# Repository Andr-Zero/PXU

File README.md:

# PXU - Replacement Power Supply for the Orignial Xbox!

## 🛑 VERY IMPORTANT SAFETY DISCLAIMER 🛑
This project involves working with and replacing a power supply unit that was originally designed to handle mains voltage. The original OEM power supply can retain a lethal electrical charge long after it has been unplugged. Proceed with extreme caution.

 **HIGH VOLTAGE RISK**: You are solely responsible for your safety. Improper handling of electronics can lead to serious injury, death, or fire. If you are not experienced and confident in working with electronics, do not attempt to install this hardware.

**USE AT YOUR OWN RISK**: This is a hobbyist project provided "as is" without warranties of any kind. The author, Andr0, is not responsible for any damage to your console, other property, or any personal injury that may occur from the use or misuse of this hardware.
___
## Features
-   ✨Support 1.0 through 1.6 revisions consoles! ✨  
    *1.0/1.1 requires the proper 12-pin connector.  
    *Switching between 1.0-1.4 and 1.6s requires changing several zero ohm resistors, documented on bottom of the PCB.
-   Accepts any DC input from 16-20V, 100W+ (Including 100W USB-C PD chargers).
-   Features user-replaceable input modules.
-   Designed as a direct swap with the OEM power supply, using the same mounting points.

## Installation
**Warning:** The OEM power supply can be dangerous even after being unplugged for long periods. Proceed with caution!

1.  **Make sure the AC power cord is unplugged from the wall!** Then, press the Xbox's power button a few times to help discharge any residual power.
2.  Open the console and remove the hard drive tray.
3.  Unplug the cable connecting the OEM power supply to the mainboard.
4.  Remove the two screws holding the power supply down. Slide it toward the front of the console just enough to disengage it from the shell's retaining clips.
5.  The power supply should now lift out. You may need to angle it to get it out of the shell.
6.  Installation is the reverse of this process.

## FAQ
**Will my "******"  work as a power source?** I cannot test every power source available. I have personally tested an MSI laptop charger (180W) and an Anker 100W USB-C charger. Similar adapters that meet the specification of 16-20V and can deliver 100W or more should work.

**Can you add feature "X"?** The goal of the main PXU board is to be a drop-in replacement that powers the console just like the OEM supply. Additional features can and should be added as daughterboards using the provided mount points.

**I dont see the USB-C Board Here.** That's in another repo: https://github.com/Andr-Zero/PXU-C-PIM

## License

This project is open-source hardware, licensed under the **CERN-OHL-S v2** (CERN Open Hardware Licence - Strongly Reciprocal).

**Copyright © 2025 Andr0**

You are free to:

-   **Use and reproduce** this design for any purpose.
-   **Modify** the design to fit your needs.  
-   **Distribute** the original design or your modifications.

In return, you must:

-   **Give credit**
-   **Share your changes** under the same CERN-OHL-S v2 license.
-  **Keep all copyright and license notices intact.** As a condition of the license's attribution requirement, all original markings on the PCB silkscreen must be retained. This includes the copyright notice, the PXU and Team Resurgent logos, and any project URLs present in the original design files. These should not be removed or altered.

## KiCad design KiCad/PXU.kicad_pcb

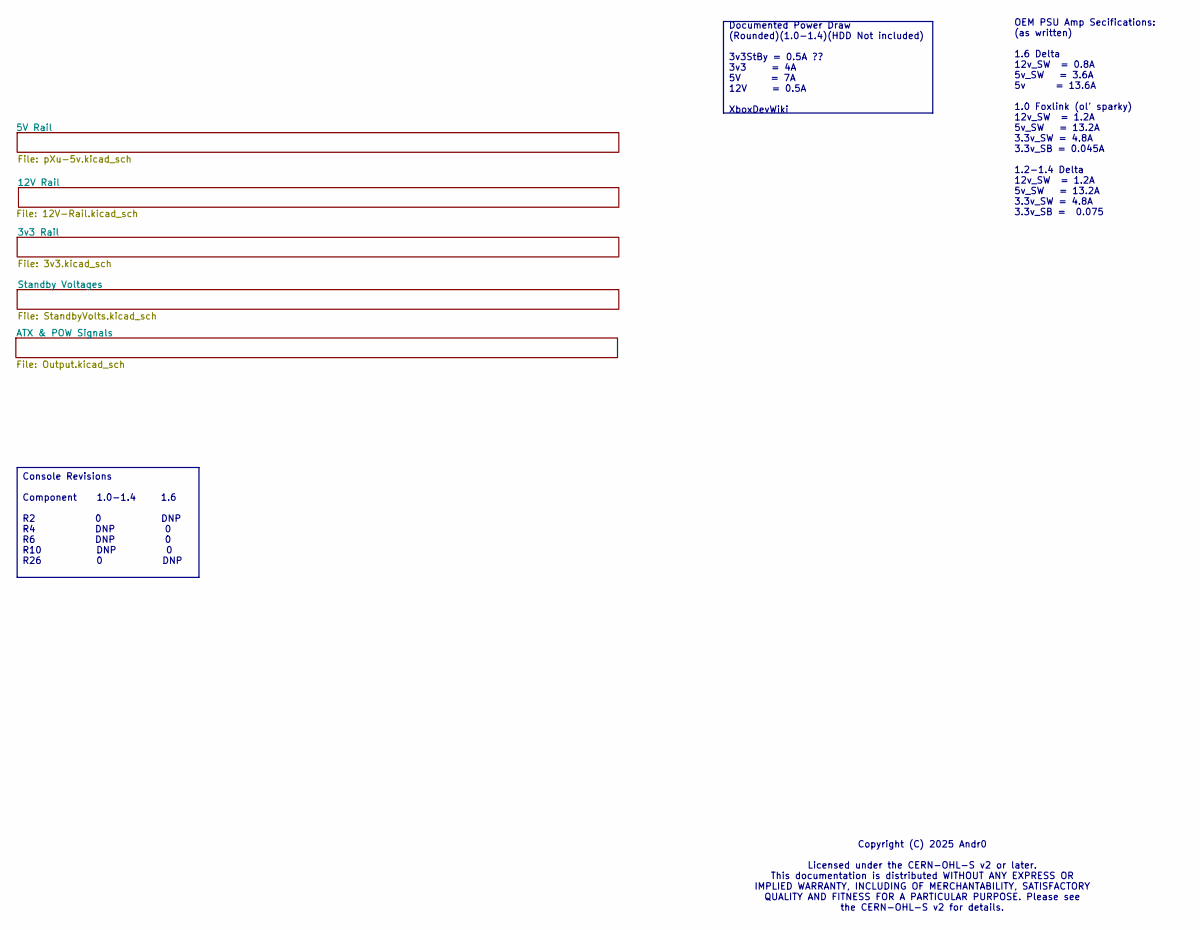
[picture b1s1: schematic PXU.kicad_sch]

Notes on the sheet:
OEM PSU Amp Secifications: (as written) 1.6 Delta 12v_SW = 0.8A 5v_SW = 3.6A 5v = 13.6A 1.0 Foxlink (ol' sparky) 12v_SW = 1.2A 5v_SW = 13.2A 3.3v_SW = 4.8A 3.3v_SB = 0.045A 1.2-1.4 Delta 12v_SW = 1.2A 5v_SW = 13.2A 3.3v_SW = 4.8A 3.3v_SB = 0.075
Copyright (C) 2025 Andr0 Licensed under the CERN-OHL-S v2 or later. This documentation is distributed WITHOUT ANY EXPRESS OR IMPLIED WARRANTY, INCLUDING OF MERCHANTABILITY, SATISFACTORY QUALITY AND FITNESS FOR A PARTICULAR PURPOSE. Please see the CERN-OHL-S v2 for details.
Console Revisions Component 1.0-1.4 1.6 R2 0 DNP R4 DNP 0 R6 DNP 0 R10 DNP 0 R26 0 DNP
Documented Power Draw (Rounded)(1.0-1.4)(HDD Not included) 3v3StBy = 0.5A ?? 3v3 = 4A 5V = 7A 12V = 0.5A XboxDevWiki

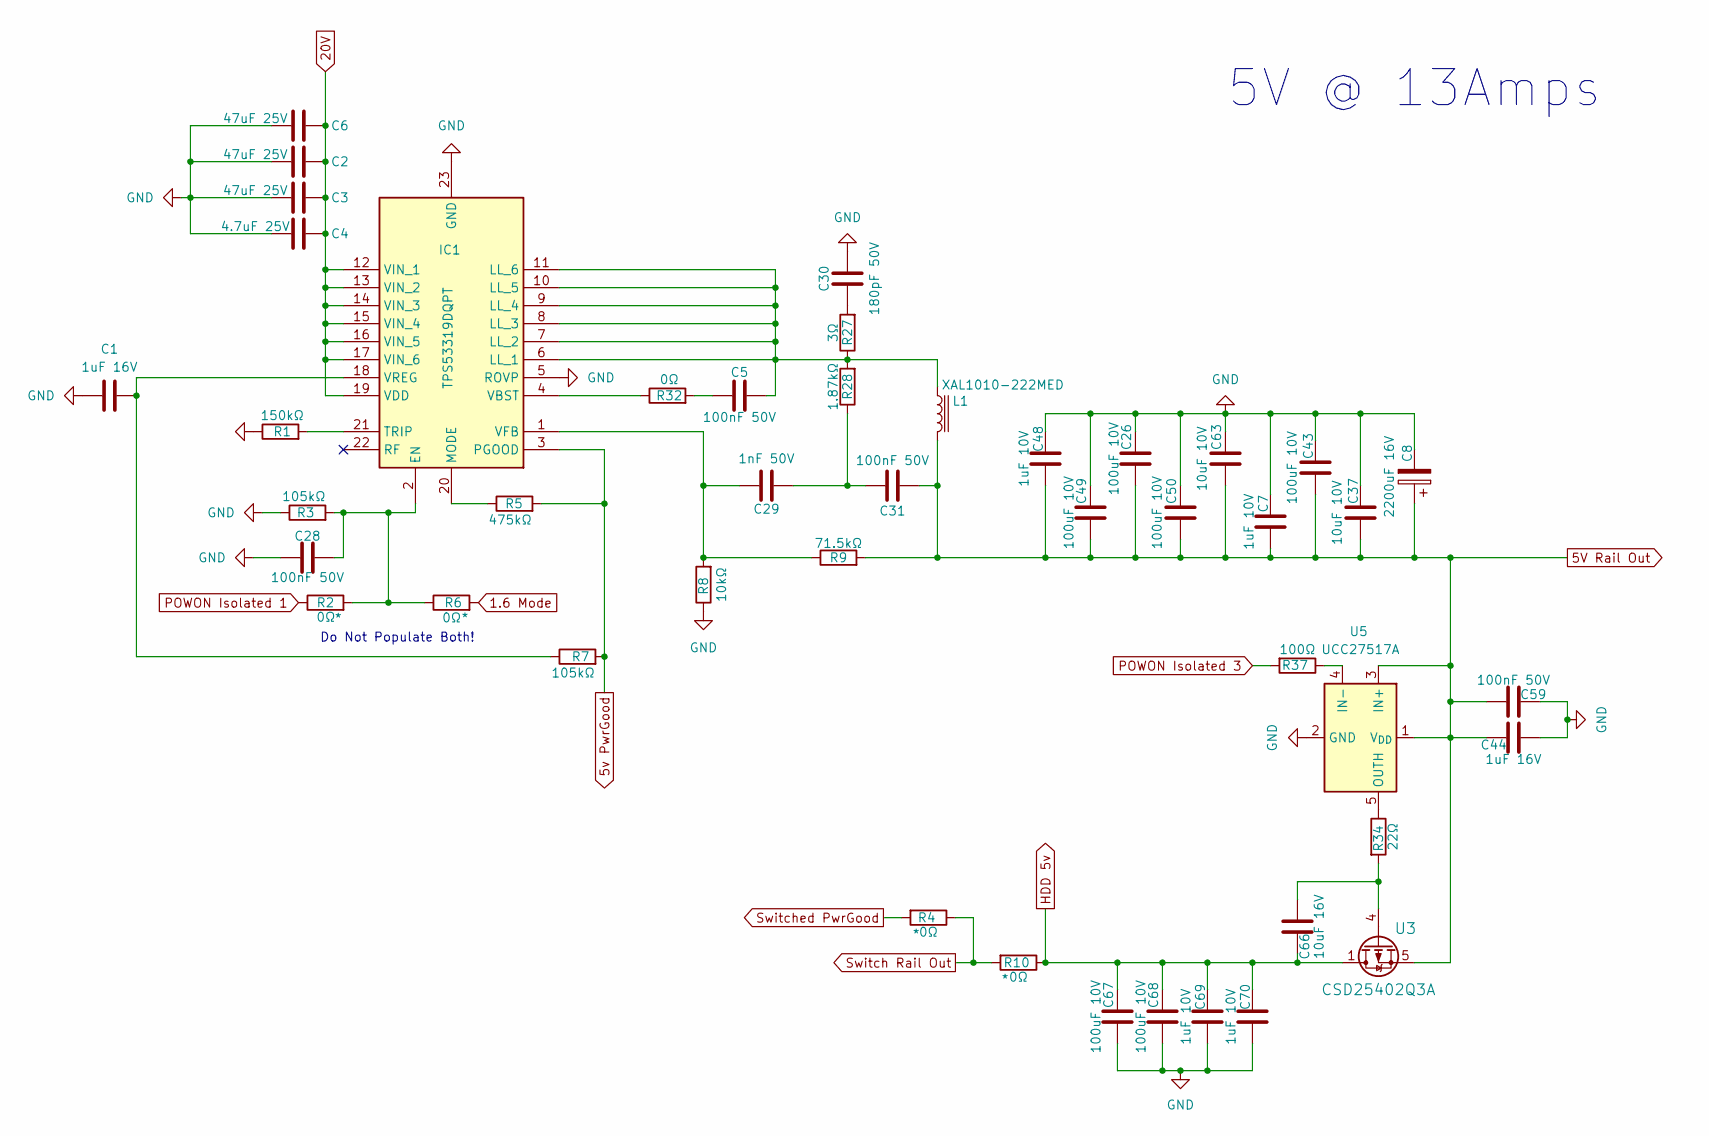
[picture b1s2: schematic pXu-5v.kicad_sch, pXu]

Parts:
C1, C44: 1uF 16V; C_0603_1608Metric_Pad1.08x0.95mm_HandSolder
C2, C3, C6: 47uF 25V; C_1210_3225Metric_Pad1.33x2.70mm_HandSolder
C4: 4.7uF 25V; C_0603_1608Metric_Pad1.08x0.95mm_HandSolder
C5, C28, C31, C59: 100nF 50V; C_0603_1608Metric_Pad1.08x0.95mm_HandSolder
C7, C48, C69, C70: 1uF 10V; C_0603_1608Metric_Pad1.08x0.95mm_HandSolder
C8: 2200uF 16V; CP_Radial_D10.0mm_P5.00mm
C26, C43, C49, C50, C67, C68: 100uF 10V; C_1206_3216Metric_Pad1.33x1.80mm_HandSolder
C29: 1nF 50V; C_0603_1608Metric_Pad1.08x0.95mm_HandSolder
C30: 180pF 50V; C_0603_1608Metric_Pad1.08x0.95mm_HandSolder
C37, C63: 10uF 10V; C_0805_2012Metric_Pad1.18x1.45mm_HandSolder
C66: 10uF 16V; C_0603_1608Metric_Pad1.08x0.95mm_HandSolder
IC1: TPS53319DQPT; SON50P500X600X150-23N-D; Mouser Part Number 595-TPS53319DQPT
L1: XAL1010-222MED; L_10.4x10.4_H4.8; Part# XAL1010-222MED
R1: 150kΩ; R_0603_1608Metric_Pad0.98x0.95mm_HandSolder
R2, R4, R6, R32: 0Ω; R_0603_1608Metric_Pad0.98x0.95mm_HandSolder
R3, R7: 105kΩ; R_0603_1608Metric_Pad0.98x0.95mm_HandSolder
R5: 475kΩ; R_0603_1608Metric_Pad0.98x0.95mm_HandSolder
R8: 10kΩ; R_0603_1608Metric_Pad0.98x0.95mm_HandSolder
R9: 71.5kΩ; R_0603_1608Metric_Pad0.98x0.95mm_HandSolder
R10: 0Ω; R_1206_3216Metric_Pad1.30x1.75mm_HandSolder
R27: 3Ω; R_1206_3216Metric_Pad1.30x1.75mm_HandSolder
R28: 1.87kΩ; R_0805_2012Metric_Pad1.20x1.40mm_HandSolder
R34: 22Ω; R_0603_1608Metric_Pad0.98x0.95mm_HandSolder
R37: 100Ω; R_0603_1608Metric_Pad0.98x0.95mm_HandSolder
U3: CSD25402Q3A; VSON-8_3.3x3.3mm_P0.65mm_NexFET
U5: UCC27517A; SOT-23-5

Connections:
1.6 Mode: R6.2; also elsewhere on the board
5V Rail Out: C7.2, C8.1, C26.2, C31.1, C37.2, C43.2, C44.1, C48.2, C49.2, C50.2, C59.2, C63.2, L1.2, R9.2, U3.5 (S), U5.1 (V_{DD}), U5.3 (IN+); also elsewhere on the board
5v PwrGood: IC1.3 (PGOOD), R5.2, R7.2; also elsewhere on the board
20V: C2.2, C3.2, C4.2, C6.2, IC1.12 (VIN_1), IC1.13 (VIN_2), IC1.14 (VIN_3), IC1.15 (VIN_4), IC1.16 (VIN_5), IC1.17 (VIN_6), IC1.19 (VDD); also elsewhere on the board
GND: C1.1, C2.1, C3.1, C4.1, C6.1, C7.1, C8.2, C26.1, C28.1, C30.2, C37.1, C43.1, C44.2, C48.1, C49.1, C50.1, C59.1, C63.1, C67.2, C68.2, C69.2, C70.2, IC1.5 (ROVP), IC1.23 (GND), R1.1, R3.1, R8.1, U5.2 (GND); also elsewhere on the board
HDD 5v: C66.1, C67.1, C68.1, C69.1, C70.1, R10.1, U3.1 (D), U3.2 (D), U3.3 (D); also elsewhere on the board
unnamed: C5.2, R32.2
unnamed: C29.1, C31.2, R28.1
unnamed: C30.1, R27.2
unnamed: C28.2, IC1.2 (EN), R2.2, R3.2, R6.1
unnamed: C5.1, IC1.6 (LL_1), IC1.7 (LL_2), IC1.8 (LL_3), IC1.9 (LL_4), IC1.10 (LL_5), IC1.11 (LL_6), L1.1, R27.1, R28.2
unnamed: IC1.20 (MODE), R5.1
unnamed: IC1.21 (TRIP), R1.2
unnamed: IC1.4 (VBST), R32.1
unnamed: C29.2, IC1.1 (VFB), R8.2, R9.1
unnamed: C1.2, IC1.18 (VREG), R7.1
unnamed: C66.2, R34.2, U3.4 (G)
unnamed: R37.1, U5.4 (IN-)
unnamed: R34.1, U5.5 (OUTH)
POWON Isolated 1: R2.1; also elsewhere on the board
POWON Isolated 3: R37.2; also elsewhere on the board
Switch Rail Out: R4.1, R10.2; also elsewhere on the board
Switched PwrGood: R4.2; also elsewhere on the board

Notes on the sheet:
Do Not Populate Both!
5V @ 13Amps

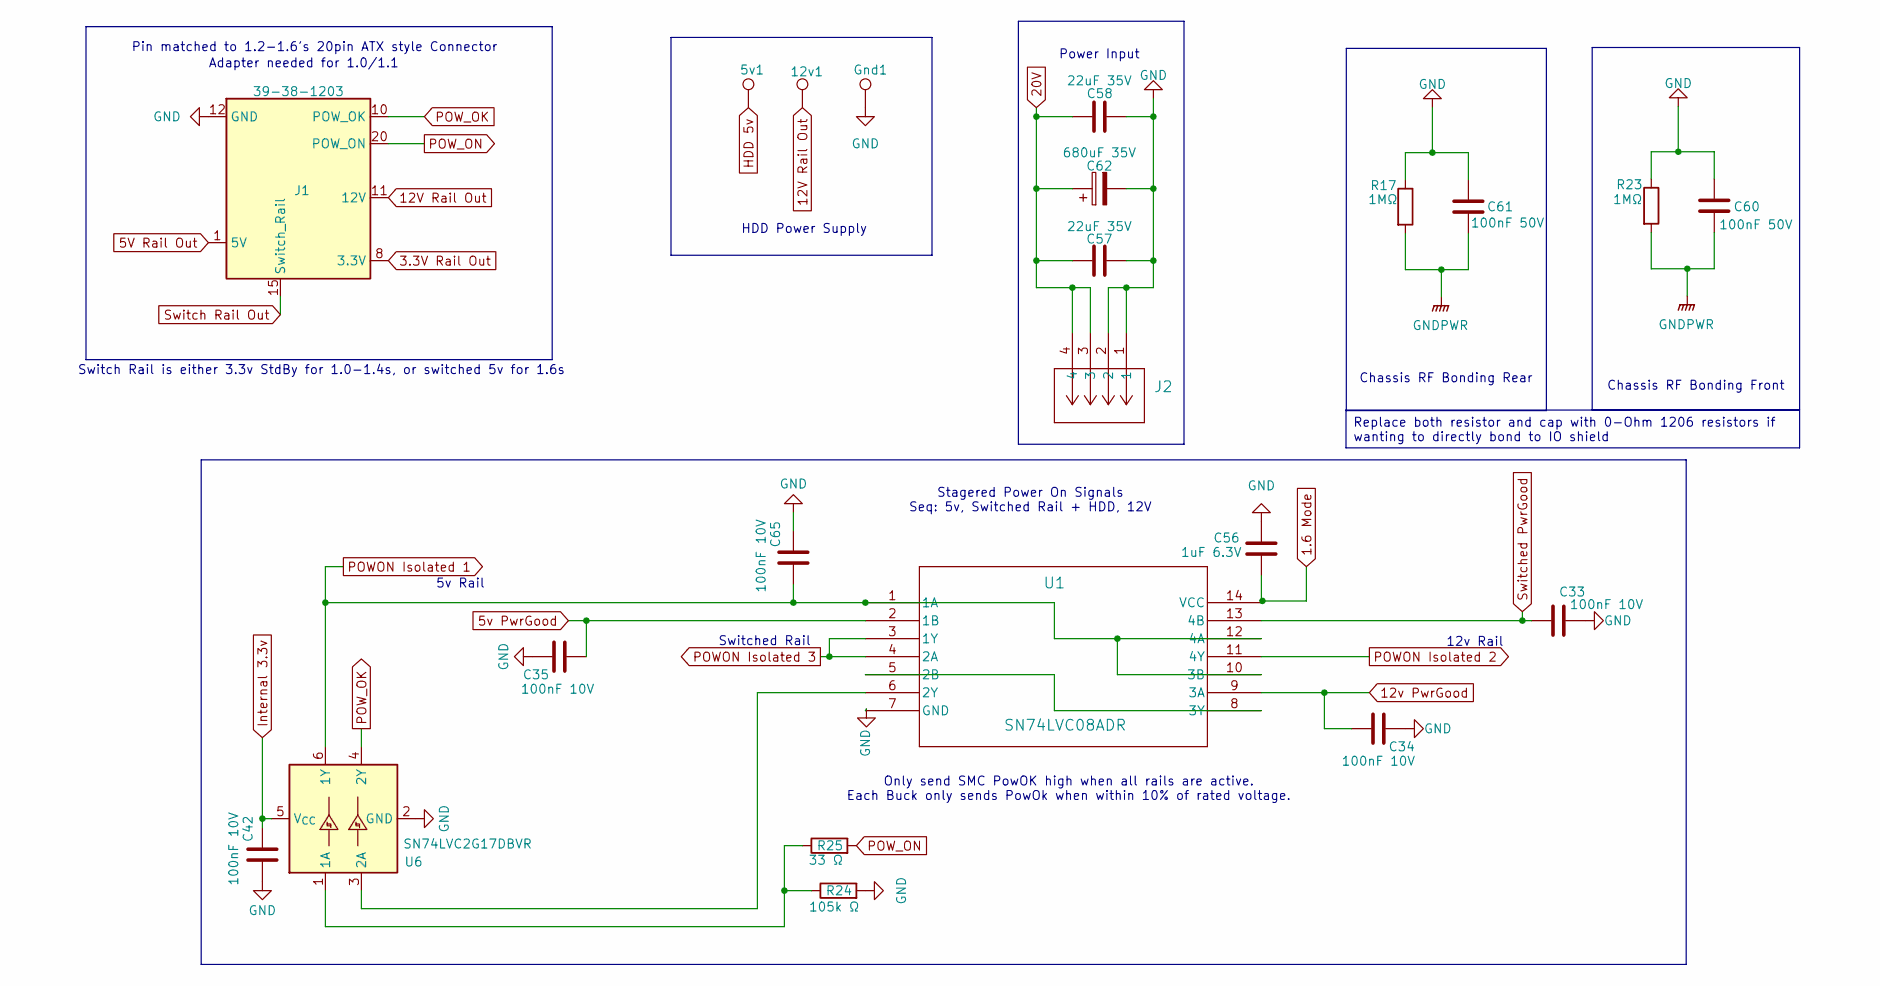
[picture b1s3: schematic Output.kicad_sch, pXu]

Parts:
5v1, 12v1: TestPoint; TestPoint_THTPad_D4.0mm_Drill2.0mm
C33, C34, C35, C42, C65: 100nF 10V; C_0603_1608Metric_Pad1.08x0.95mm_HandSolder
C56: 1uF 6.3V; C_0603_1608Metric_Pad1.08x0.95mm_HandSolder
C57, C58: 22uF 35V; C_1210_3225Metric_Pad1.33x2.70mm_HandSolder
C60, C61: 100nF 50V; C_1206_3216Metric_Pad1.33x1.80mm_HandSolder
C62: 680uF 35V; CP_Radial_D10.0mm_P5.00mm
Gnd1: TestPoint; TestPoint_THTPad_D4.0mm_Drill2.0mm
J1: 39-38-1203; Molex_Mini-Fit_Jr_5566-20A_2x10_P4.20mm_Vertical
J2: 171826-4; CONN_171826-4_TYCO_TYC
R17, R23: 1MΩ; R_1206_3216Metric_Pad1.30x1.75mm_HandSolder
R24: 105k Ω; R_0603_1608Metric_Pad0.98x0.95mm_HandSolder
R25: 33 Ω; R_0603_1608Metric_Pad0.98x0.95mm_HandSolder
U1: SN74LVC08ADR; D14
U6: SN74LVC2G17DBVR; SOT-23-6_Handsoldering

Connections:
1.6 Mode: C42.2, C56.2, U1.14 (VCC), U6.5 (V_{CC}); also elsewhere on the board
3.3V Rail Out: J1.7 (3.3V), J1.8 (3.3V), J1.17 (3.3V), J1.18 (3.3V); also elsewhere on the board
5V Rail Out: J1.1 (5V), J1.2 (5V), J1.3 (5V), J1.13 (5V); also elsewhere on the board
5v PwrGood: C35.2, U1.2 (1B); also elsewhere on the board
12V Rail Out: 12v1.1, J1.11 (12V); also elsewhere on the board
12v PwrGood: C34.1, U1.9 (3A); also elsewhere on the board
20V: C57.1, C58.1, C62.1, J2.3, J2.4; also elsewhere on the board
GND: C33.1, C34.2, C35.1, C42.1, C56.1, C57.2, C58.2, C60.1, C61.1, C62.2, C65.1, Gnd1.1, J1.4 (GND), J1.5 (GND), J1.6 (GND), J1.9 (GND), J1.12 (GND), J1.14 (GND), J1.16 (GND), J1.19 (GND), J2.1, J2.2, R17.1, R23.1, R24.2, U1.7 (GND), U6.2 (GND); also elsewhere on the board
GNDPWR: C60.2, C61.2, R17.2, R23.2
unnamed: U1.5 (2B), U1.8 (3Y)
unnamed: U1.6 (2Y), U6.3 (2A)
unnamed: R24.1, R25.1, U6.1 (1A)
POWON Isolated 1: C65.2, U1.1 (1A), U1.10 (3B), U1.12 (4A), U6.6 (1Y); also elsewhere on the board
POWON Isolated 2: U1.11 (4Y); also elsewhere on the board
POWON Isolated 3: U1.3 (1Y), U1.4 (2A); also elsewhere on the board
POW_OK: J1.10 (POW_OK), U6.4 (2Y)
POW_ON: J1.20 (POW_ON), R25.2
Switch Rail Out: J1.15 (Switch_Rail); also elsewhere on the board
Switched PwrGood: C33.2, U1.13 (4B); also elsewhere on the board

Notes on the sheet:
HDD Power Supply
Switched Rail
Chassis RF Bonding Rear
Adapter needed for 1.0/1.1
Pin matched to 1.2-1.6's 20pin ATX style Connector
Stagered Power On Signals Seq: 5v, Switched Rail + HDD, 12V
12v Rail
Only send SMC PowOK high when all rails are active. Each Buck only sends PowOk when within 10% of rated voltage.
Power Input
Chassis RF Bonding Front
5v Rail
Switch Rail is either 3.3v StdBy for 1.0-1.4s, or switched 5v for 1.6s
Replace both resistor and cap with 0-Ohm 1206 resistors if wanting to directly bond to IO shield

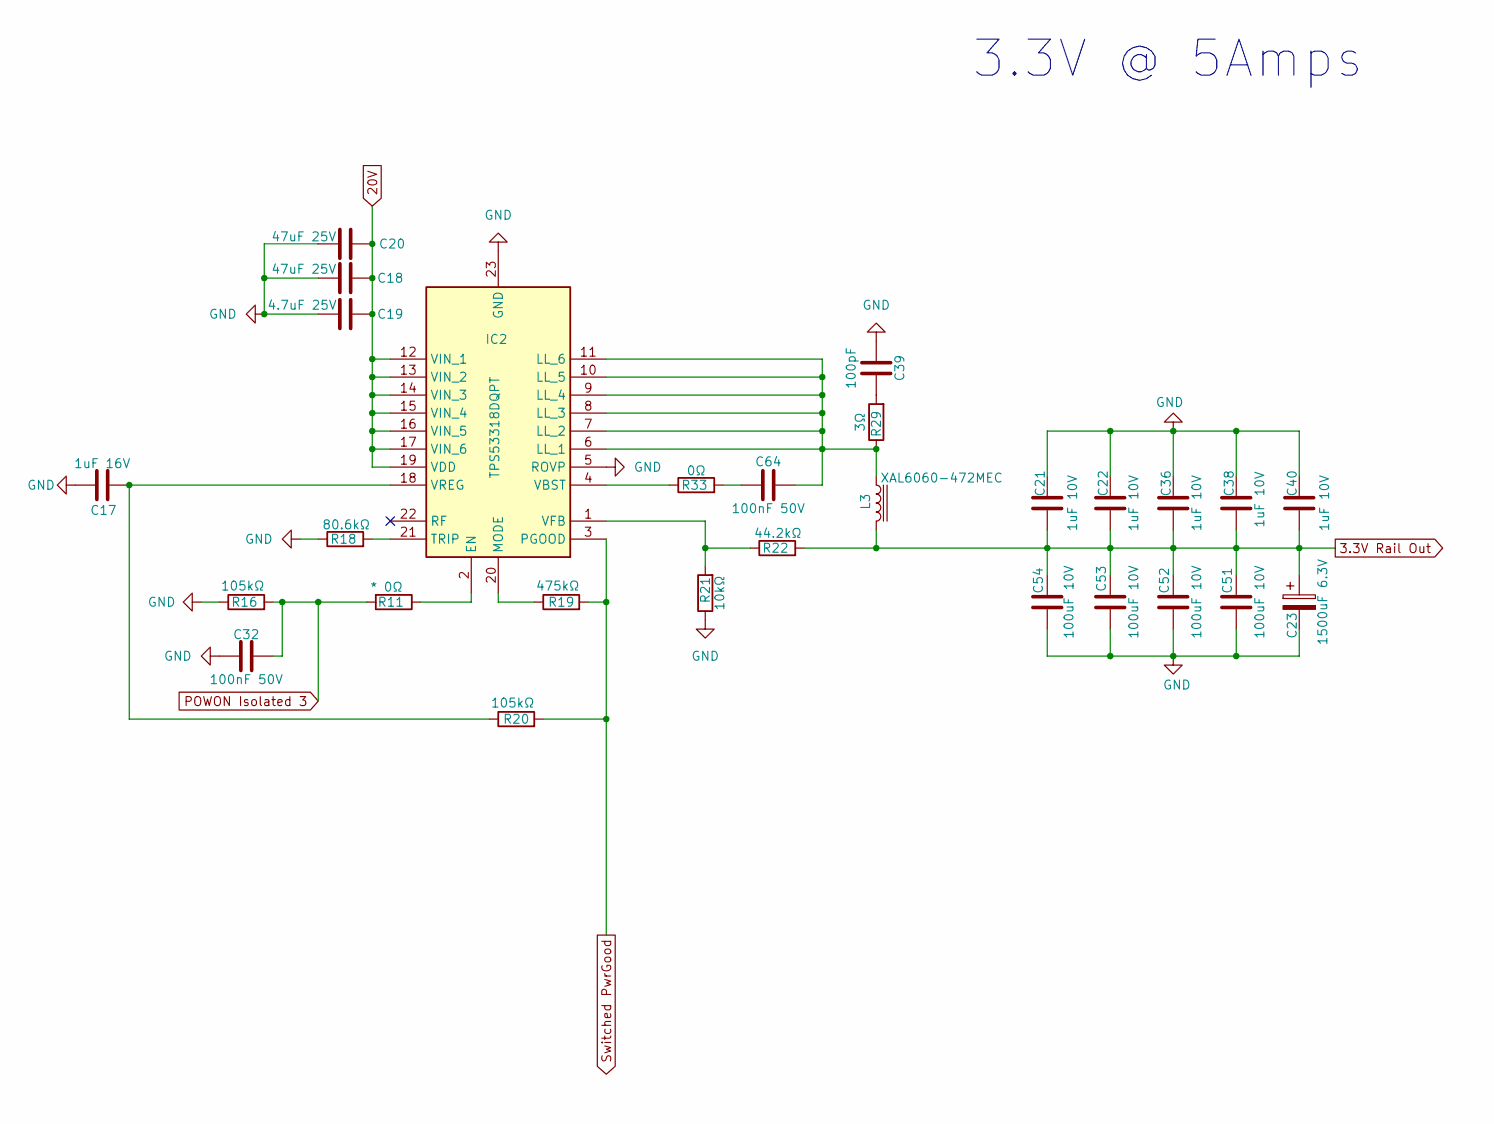
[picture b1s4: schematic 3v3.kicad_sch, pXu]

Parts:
C17: 1uF 16V; C_0603_1608Metric_Pad1.08x0.95mm_HandSolder
C18, C20: 47uF 25V; C_1210_3225Metric_Pad1.33x2.70mm_HandSolder
C19: 4.7uF 25V; C_0603_1608Metric_Pad1.08x0.95mm_HandSolder
C21, C22, C36, C38, C40: 1uF 10V; C_0603_1608Metric_Pad1.08x0.95mm_HandSolder
C23: 1500uF 6.3V; CP_Radial_D10.0mm_P5.00mm
C32, C64: 100nF 50V; C_0603_1608Metric_Pad1.08x0.95mm_HandSolder
C39: 100pF; C_0603_1608Metric_Pad1.08x0.95mm_HandSolder; Voltage 50V
C51, C52, C53, C54: 100uF 10V; C_1206_3216Metric_Pad1.33x1.80mm_HandSolder
IC2: TPS53318DQPT; SON50P500X600X150-23N-D; Mouser Part Number 595-TPS53319DQPT
L3: XAL6060-472MEC; L_6.3x6.3_H3; Part# XAL6060-472MEC
R11, R33: 0Ω; R_0603_1608Metric_Pad0.98x0.95mm_HandSolder
R16, R20: 105kΩ; R_0603_1608Metric_Pad0.98x0.95mm_HandSolder
R18: 80.6kΩ; R_0603_1608Metric_Pad0.98x0.95mm_HandSolder
R19: 475kΩ; R_0603_1608Metric_Pad0.98x0.95mm_HandSolder
R21: 10kΩ; R_0603_1608Metric_Pad0.98x0.95mm_HandSolder
R22: 44.2kΩ; R_0603_1608Metric_Pad0.98x0.95mm_HandSolder
R29: 3Ω; R_0805_2012Metric_Pad1.20x1.40mm_HandSolder

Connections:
3.3V Rail Out: C21.2, C22.2, C23.1, C36.2, C38.2, C40.2, C51.1, C52.1, C53.1, C54.1, L3.2, R22.2; also elsewhere on the board
20V: C18.2, C19.2, C20.2, IC2.12 (VIN_1), IC2.13 (VIN_2), IC2.14 (VIN_3), IC2.15 (VIN_4), IC2.16 (VIN_5), IC2.17 (VIN_6), IC2.19 (VDD); also elsewhere on the board
GND: C17.1, C18.1, C19.1, C20.1, C21.1, C22.1, C23.2, C32.1, C36.1, C38.1, C39.1, C40.1, C51.2, C52.2, C53.2, C54.2, IC2.5 (ROVP), IC2.23 (GND), R16.1, R18.1, R21.1; also elsewhere on the board
unnamed: C39.2, R29.2
unnamed: C64.2, R33.2
unnamed: IC2.2 (EN), R11.1
unnamed: C64.1, IC2.6 (LL_1), IC2.7 (LL_2), IC2.8 (LL_3), IC2.9 (LL_4), IC2.10 (LL_5), IC2.11 (LL_6), L3.1, R29.1
unnamed: IC2.20 (MODE), R19.1
unnamed: IC2.21 (TRIP), R18.2
unnamed: IC2.4 (VBST), R33.1
unnamed: IC2.1 (VFB), R21.2, R22.1
unnamed: C17.2, IC2.18 (VREG), R20.1
POWON Isolated 3: C32.2, R11.2, R16.2; also elsewhere on the board
Switched PwrGood: IC2.3 (PGOOD), R19.2, R20.2; also elsewhere on the board

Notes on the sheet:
3.3V @ 5Amps

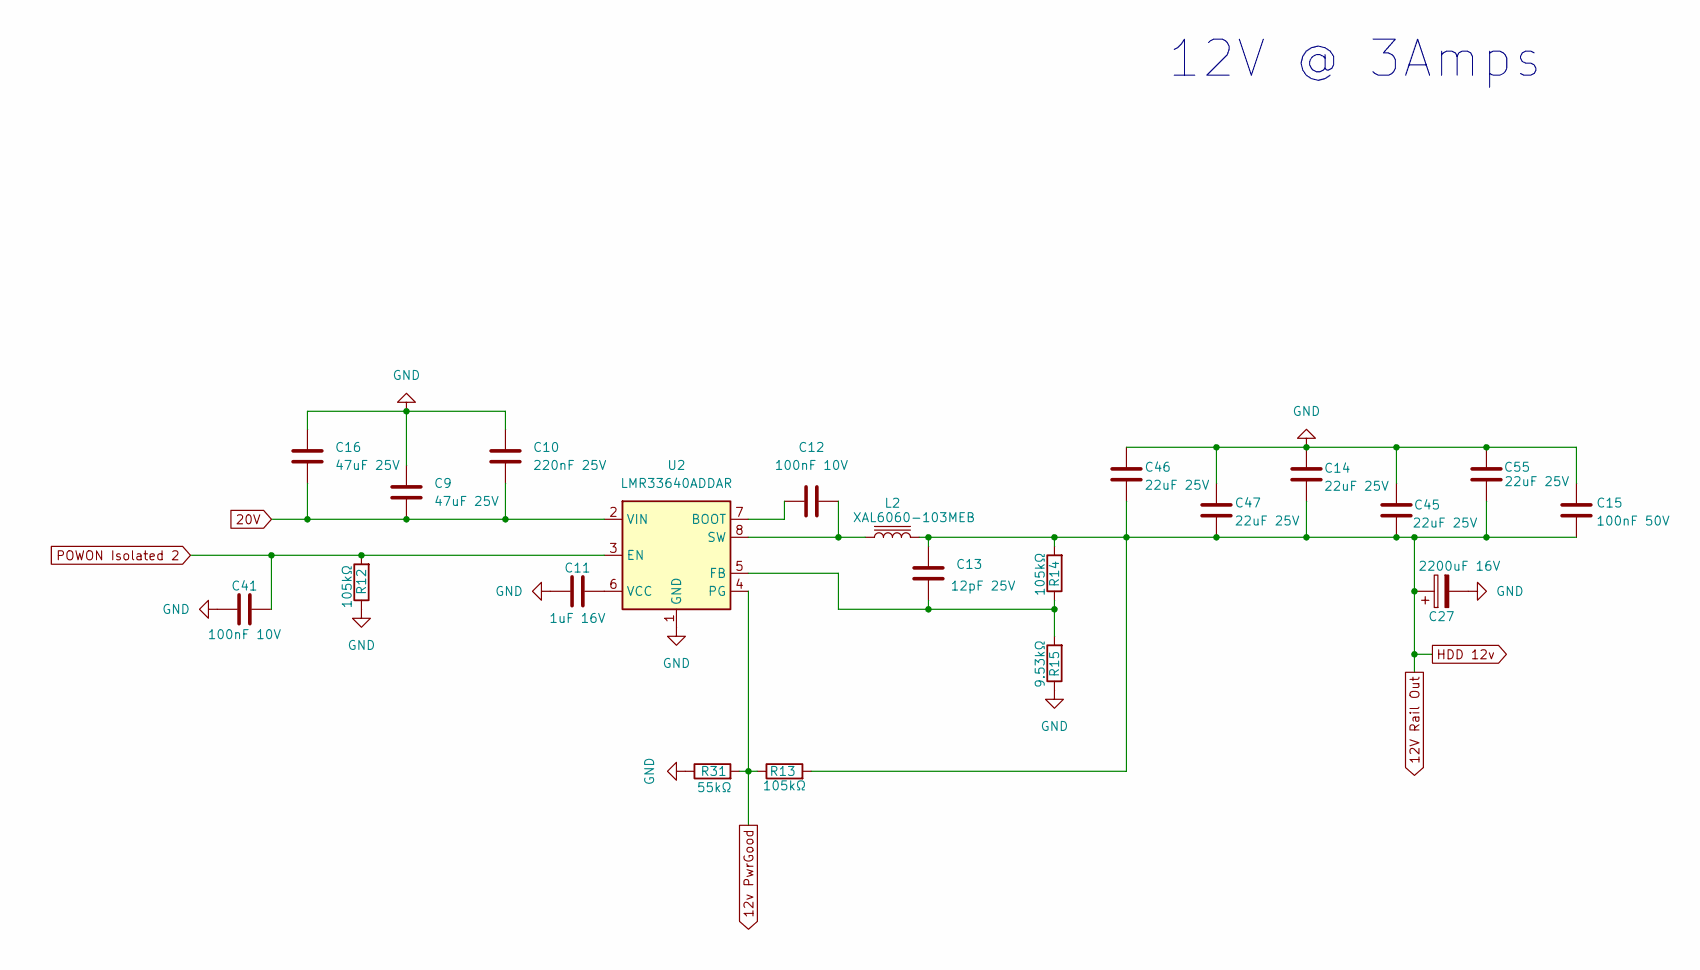
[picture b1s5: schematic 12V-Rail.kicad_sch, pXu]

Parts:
C9, C16: 47uF 25V; C_1210_3225Metric_Pad1.33x2.70mm_HandSolder
C10: 220nF 25V; C_0805_2012Metric_Pad1.18x1.45mm_HandSolder
C11: 1uF 16V; C_0603_1608Metric_Pad1.08x0.95mm_HandSolder
C12, C41: 100nF 10V; C_0603_1608Metric_Pad1.08x0.95mm_HandSolder
C13: 12pF 25V; C_0603_1608Metric_Pad1.08x0.95mm_HandSolder
C14, C45, C46, C47, C55: 22uF 25V; C_0805_2012Metric_Pad1.18x1.45mm_HandSolder
C15: 100nF 50V; C_0603_1608Metric_Pad1.08x0.95mm_HandSolder
C27: 2200uF 16V; CP_Radial_D10.0mm_P5.00mm
L2: XAL6060-103MEB; L_6.3x6.3_H3; Part# XAL6060-682MEB
R12, R13, R14: 105kΩ; R_0603_1608Metric_Pad0.98x0.95mm_HandSolder
R15: 9.53kΩ; R_0603_1608Metric_Pad0.98x0.95mm_HandSolder
R31: 55kΩ; R_0603_1608Metric_Pad0.98x0.95mm_HandSolder
U2: LMR33640ADDAR; Texas_HSOP-8-1EP_3.9x4.9mm_P1.27mm_ThermalVias

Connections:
12V Rail Out: C13.2, C14.2, C15.1, C27.1, C45.2, C46.2, C47.2, C55.1, L2.2, R13.2, R14.2; also elsewhere on the board
12v PwrGood: R13.1, R31.2, U2.4 (PG); also elsewhere on the board
20V: C9.2, C10.2, C16.2, U2.2 (VIN); also elsewhere on the board
GND: C9.1, C10.1, C11.1, C14.1, C15.2, C16.1, C27.2, C41.1, C45.1, C46.1, C47.1, C55.2, R12.1, R15.1, R31.1, U2.1 (GND), U2.9 (GND); also elsewhere on the board
unnamed: C12.1, U2.7 (BOOT)
unnamed: C13.1, R14.1, R15.2, U2.5 (FB)
unnamed: C12.2, L2.1, U2.8 (SW)
unnamed: C11.2, U2.6 (VCC)
POWON Isolated 2: C41.2, R12.2, U2.3 (EN); also elsewhere on the board

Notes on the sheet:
12V @ 3Amps

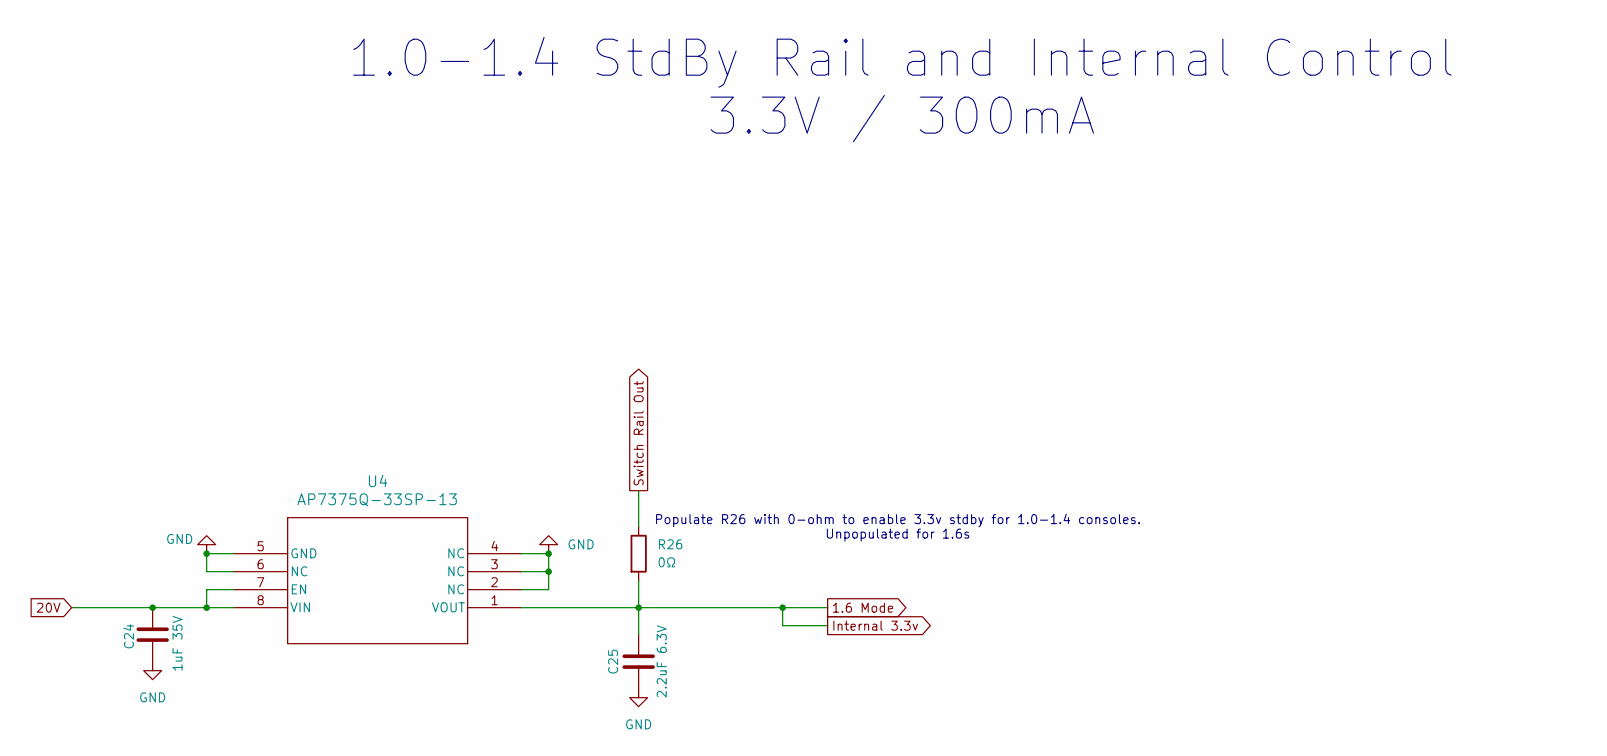
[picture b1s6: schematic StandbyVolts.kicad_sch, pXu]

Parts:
C24: 1uF 35V; C_0603_1608Metric_Pad1.08x0.95mm_HandSolder
C25: 2.2uF 6.3V; C_0603_1608Metric_Pad1.08x0.95mm_HandSolder
R26: 0Ω; R_0603_1608Metric_Pad0.98x0.95mm_HandSolder
U4: AP7375Q-33SP-13; SO-8EP_DIO

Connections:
1.6 Mode: C25.1, R26.2, U4.1 (VOUT); also elsewhere on the board
20V: C24.1, U4.7 (EN), U4.8 (VIN); also elsewhere on the board
GND: C24.2, C25.2, U4.2 (NC), U4.3 (NC), U4.4 (NC), U4.5 (GND), U4.6 (NC); also elsewhere on the board
Switch Rail Out: R26.1; also elsewhere on the board

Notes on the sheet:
Populate R26 with 0-ohm to enable 3.3v stdby for 1.0-1.4 consoles. Unpopulated for 1.6s
1.0-1.4 StdBy Rail and Internal Control 3.3V / 300mA

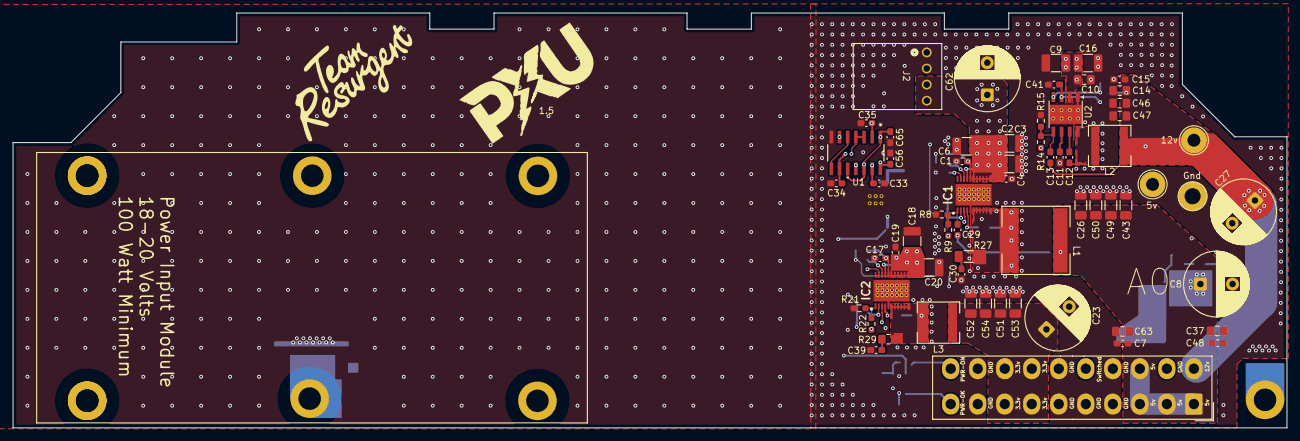
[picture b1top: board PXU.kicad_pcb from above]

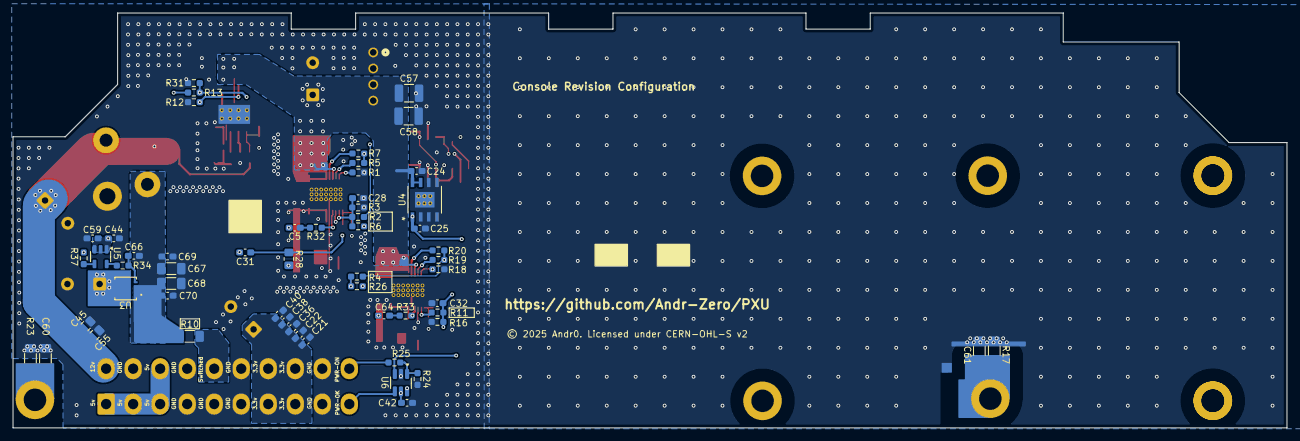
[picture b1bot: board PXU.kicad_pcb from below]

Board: 4 copper layers, 198.0 x 64.5 mm, 120 parts (56 on the bottom side), 46 nets.

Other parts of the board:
5v, 12v: TestPoint; TestPoint_THTPad_D4.0mm_Drill2.0mm
Gnd: TestPoint; TestPoint_THTPad_D4.0mm_Drill2.0mm

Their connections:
12V Rail Out: 12v.1; also elsewhere on the board
GND: Gnd.1; also elsewhere on the board
HDD 5v: 5v.1; also elsewhere on the board

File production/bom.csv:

Designator,Footprint,Quantity,Value,LCSC Part #
"_6, _5, _4, _3, _2, ",,6,,
"12V, 5V, GND",TestPoint_THTPad_D4.0mm_Drill2.0mm,3,TestPoint,
"C1, C11, C17, C44",0603,4,1uF 16V,
C10,0805,1,220nF 25V,
"C12, C33, C34, C35, C41, C42, C65",0603,7,100nF 10V,
C13,0603,1,12pF 25V,
"C14, C45, C46, C47, C55",0805,5,22uF 25V,
"C15, C28, C31, C32, C5, C59, C64",0603,7,100nF 50V,
"C16, C18, C2, C20, C3, C6, C9",1210,7,47uF 25V,
"C19, C4",0603,2,4.7uF 25V,
"C21, C22, C36, C38, C40, C48, C69, C7, C70",0603,9,1uF 10V,
C23,CP_Radial_D10.0mm_P5.00mm,1,1500uF 6.3V,
C24,0603,1,1uF 35V,
C25,0603,1,2.2uF 6.3V,
"C26, C43, C49, C50, C51, C52, C53, C54, C67, C68",1206,10,100uF 10V,
"C27, C8",CP_Radial_D10.0mm_P5.00mm,2,2200uF 16V,
C29,0603,1,1nF 50V,
C30,0603,1,180pF,
"C37, C63",0805,2,10uF 10V,
C39,0603,1,100pF,
C56,0603,1,1uF 6.3V,
"C57, C58",1210,2,22uF 35V,
"C60, C61",1206,2,100nF 50V,
C62,CP_Radial_D10.0mm_P5.00mm,1,680uF 35V,
C66,0603,1,10uF 16V,
IC1,SON50P500X600X150-23N-D,1,TPS53319DQPT,
IC2,SON50P500X600X150-23N-D,1,TPS53318DQPT,
J1,Molex_Mini-Fit_Jr_5566-20A_2x10_P4.20mm_Vertical,1,39-38-1203,
J2,CONN_171826-4_TYCO_TYC,1,171826-4,
L1,L_10.4x10.4_H4.8,1,XAL1010-222MED,
L2,L_6.3x6.3_H3,1,XAL6060-103MEB,
L3,L_6.3x6.3_H3,1,XAL6060-472MEC,
R1,0603,1,150kΩ,
R10,1206,1,0Ω,
"R11, R2, R26, R32, R33, R4, R6",0603,7,0Ω,
"R12, R13, R14, R16, R20, R3, R7",0603,7,105kΩ,
R15,0603,1,9.53kΩ,
"R17, R23",1206,2,1MΩ,
R18,0603,1,80.6kΩ,
"R19, R5",0603,2,475kΩ,
"R21, R8",0603,2,10kΩ,
R22,0603,1,44.2kΩ,
R24,0603,1,105k Ω,
R25,0603,1,33 Ω,
R27,1206,1,3Ω,
R28,0805,1,1.87kΩ,
R29,0805,1,3Ω,
R31,0603,1,55kΩ,
R34,0603,1,22Ω,
R37,0603,1,100Ω,
R9,0603,1,71.5kΩ,
U1,D14,1,SN74LVC08ADR,
U2,Texas_HSOP-8-1EP_3.9x4.9mm_P1.27mm_ThermalVias,1,LMR33640ADDAR,
U3,CSD25402Q3A,1,CSD25402Q3A,
U4,SO-8EP_DIO,1,AP7375Q-33SP-13,
U5,SOT-23-5,1,UCC27517A,
U6,SOT-23-6_Handsoldering,1,SN74LVC2G17DBVR,

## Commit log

2025-02-22 Create README.md
    init readme
2025-03-01 Update README.md
    I hate markdown sometimes...
2025-03-30 Update README.md
    more details
2025-03-30 Update README.md
    damn markdown...
2025-03-30 Update README.md
    added pressing pwr to discarge caps. thnx eq!
2025-11-09 Initial Upload
2025-11-11 Update README.md
    Spelling errors...
2025-11-17 Update README.md
    Revised whole README
2025-11-17 License upload
    Missed including license in initial upload

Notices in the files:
KiCad/PXU.kicad_pcb:
© 2025 Andr0. Licensed under CERN-OHL-S v2
